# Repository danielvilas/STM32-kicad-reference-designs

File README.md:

# STM32-kicad-reference-designs

{:toc}

Reference Designs for STM32 in KiCad

These projects are designed as reference Design for copy subsheets and reuse wherever needed.

Ideally the board will allways the same (DevelBoard) modified to use the current chip. But as needed the reference design will be updated to use different elements, such as Ethernet, Can Bus, usb.

## Folder structure

The Folders under this repository are defined to follow this standard:
```
 .
├── [FAMILY]
│   ├── [LINE]
|   |   ├──Firmware
|   |   |  └──[*] Platformio Code
|   |   ├──[CHIP]_[Board]
|   |   |  └──[*] Kicad Project
|   |   └──README.MD
│   ├── [LINE] Other line 
|   |   └── ...
|   ...  
│   └──PlatformIo
│       ├──install.sh
│       ├──[Board].json
|       ├──[variantn].h
|       ├──[variantn].cpp
|       └── ... More boards and variants
└──[FAMILY] Other family
├──... More families
...

```
The folder estructure is based on the STM32 organization of theirs chips, this are based on families and lines. This relates to the name of the chip having the code `STM32FFLLCCCC'  where F is the FamiliyCode, L the line and C the chip code.

|Terms|Descritpion|examples|
|:--|:--|:--|
|Family |Stm32 Family | STM32F4, STM32G0 |
|Line| Stm32 Line name, chooses a model within the family| STM32F103, STM32G051|
|Chip| Current Chip, defines package, ram, rom,... inside the line| STM32F103CBT8, STM32G051C8U6|
|Firmware| Platform.io project for all boards on this family. Create envorinments for each| see notes|
|`[CHIP]_[BOARD]`| Kicad Project of board | see notes|
|README.md| each line should have it's own document to explay all the boards, what the firmware does, and the compatible chips (testeds)|
|PlatformIo|On this folder must be all the files to install the boards in PlatformIo.|b|

### Chip compatibility
By default, and as far it is indicated by ST, all the chips with the same package are interchangeables, at least at pcb level. That means that the power pins are on the same posititions and the same for the io ones.

> **_NOTE:_**  Some lines/families needs some minor changes on power pins, but the io pins mantains the positions. Check datasheets

Tested chips, should be on the README.md file of the line.

> **_NOTE:_**  This applies to hardware, not at software. update the firmware accordiling

### Firmware Notes
The firmware should be unique for the line and configured by environments on Platformio. In the case two firmwares are needed, then it will be explained on the README.MD.

The enviroments should be based on the "Generic" boards of platform.io with the defines for use the clock correctly. Even if it is based on another boards, (such as blackpill) in this cases it is correct to have two environments for that board (generic and the original board).

The environments must be explained on the README.md of the line.

The bare minimum firmware must have a blinking led and serial output (UART or USB). If the board has more components (CAN, ETH0,...) the firmware should select them by defines and have the component it's own set of files. 

### Board folder Notes
As stated before, there are compatible chips, cappable of drop-ons replacement. When a fully compatible chip is found, there is no need to copy all the board. But the folder for both chips must exists. When this case ocurrs, ensure that:

* On the original board, include notes on the schematic to include the new chip.
* On the line README.md of the original board, include the chip on the compatible chips found
* On the folder of the new chip, include:
  * Link to the current folder
  * README.MD explaing when was detected, to which, and which versions of the board are tested.
* On the line README.md of the new board document the board is the same of...

> **_NOTE:_**  Remebember that only applies to hardware, the new line must have it's own firmware, with the new chip environment.

## Kicad Project Rules
The objective is to have a series of schemeatic pages to easily import onto new projects.

The main project must only contain:
* Mount holes, or similar
* Debug Leds
* Board related connectors
* Zone for (general) power distribution, or subpage if needed
* Each functional component in one SubPage
* Mapping to the project especific pin/net names

Inside each sub page, one per functional component:
* The bare minimun componentes
* All the required connectors related to the function (SWD, ETH, USB, ...)
* Blocks separated by zones
* Herarchichal pins must be named as low level (chip) possible
* Specific power distribution as a zone, but subpage if needed

Good rules indicate to have all the conectors on the main page, but on this project we search to have a library of schematics ready to use, so it is better to have the required connectors on the same page of the functionality.

## Status of Boards

|Family|Line|Board|Status|
|:--|:--|:--|:--|
|F0|STM32F030|STM32F030K6T6|tested, updated needed|
|F1|STM32F103|STM32F103C8T8|Not implemented, tested old version|
|G0|STM32G051|STM32G051C8U6|Only in design phase|

## Change Log

* 25/05/2021 Initial Commits
  * Copy STM32F103 Devel Board from Digital Trains
* 04/08/2021 Re-Structuration
  * Creation of the structure of folders
  * Update Kicad to sub-pages
  * Added STM32G051
* 03/09/2021 Added F030
  * Added an F030
  * Created Files for board integration on pio

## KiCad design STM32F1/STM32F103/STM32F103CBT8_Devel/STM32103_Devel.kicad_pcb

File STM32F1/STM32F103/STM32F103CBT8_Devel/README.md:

# STM32F103 Devel Board
STM32F103 Board for development with STM32F103CB chip. The intention of this project is to have my own basic board for this chip in order to design custom boards which use the STM32103CB chip.

## Board specs:
* CHIP STM32F103CBT6
  * 128KB Flash / 20 KB RAM
  * 72 MHz Core
  * [https://www.st.com/en/microcontrollers-microprocessors/stm32f103cb.html](https://www.st.com/en/microcontrollers-microprocessors/stm32f103cb.html)
* Board Cristals:
  * HSE Clock: 8 Mhz
  * LSE Clokc: 32.768KHz
* Ports:
  * USB Port
  * SWD 20 pins 2.54
  * SWD 10 pins 1.27
  * PortA and PortB 16 pins 2.54
* 3.3V Regulator:
  * AMS1117-3.3
* Indicator LEDs:
  * 5V
  * 3.3V
  * PB5 (ligh on low)
* Boot selector
  * Boot0 and Boot1 to jumper pins

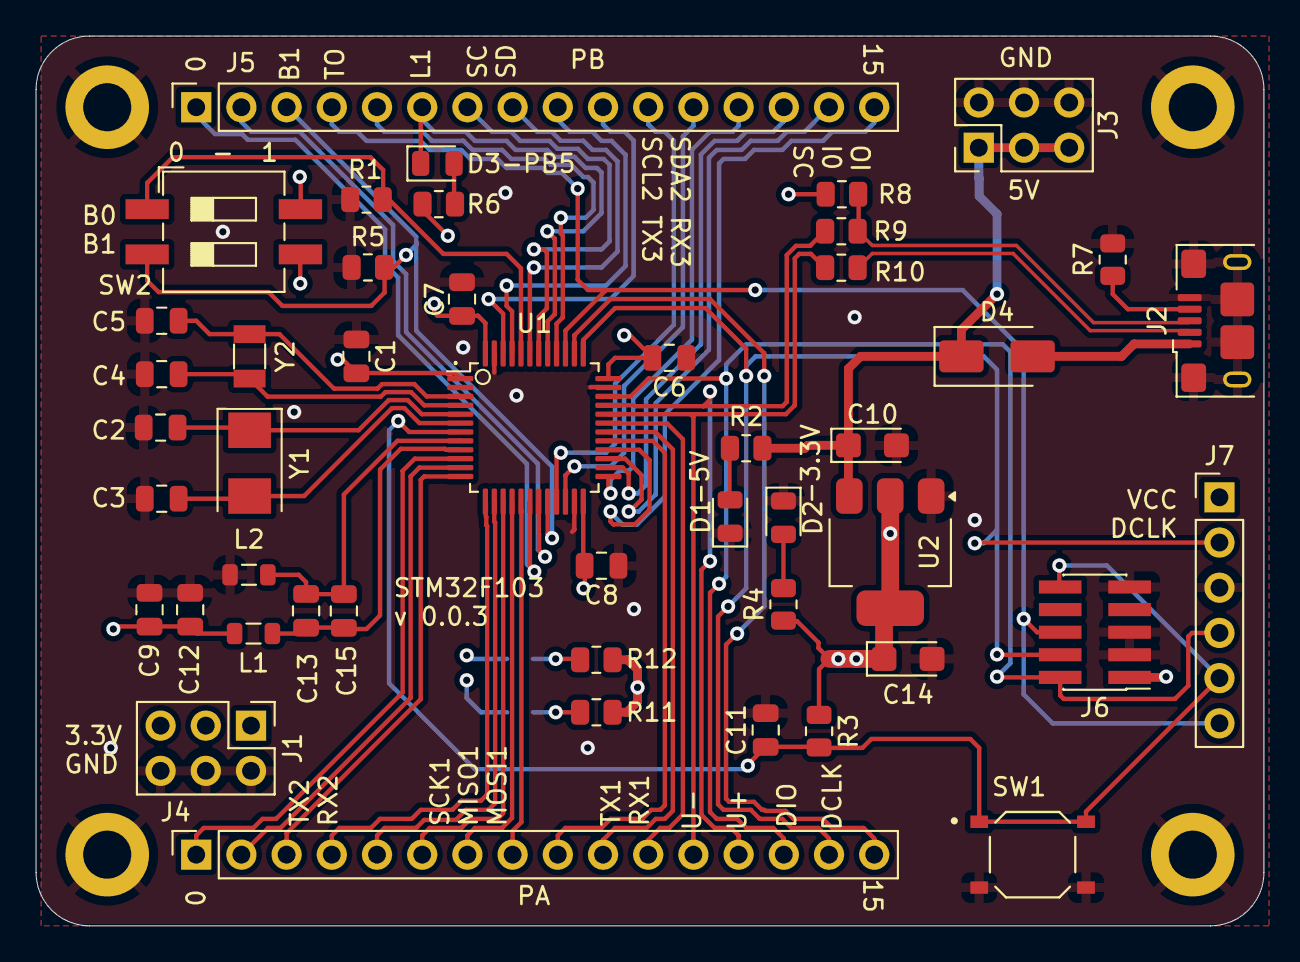
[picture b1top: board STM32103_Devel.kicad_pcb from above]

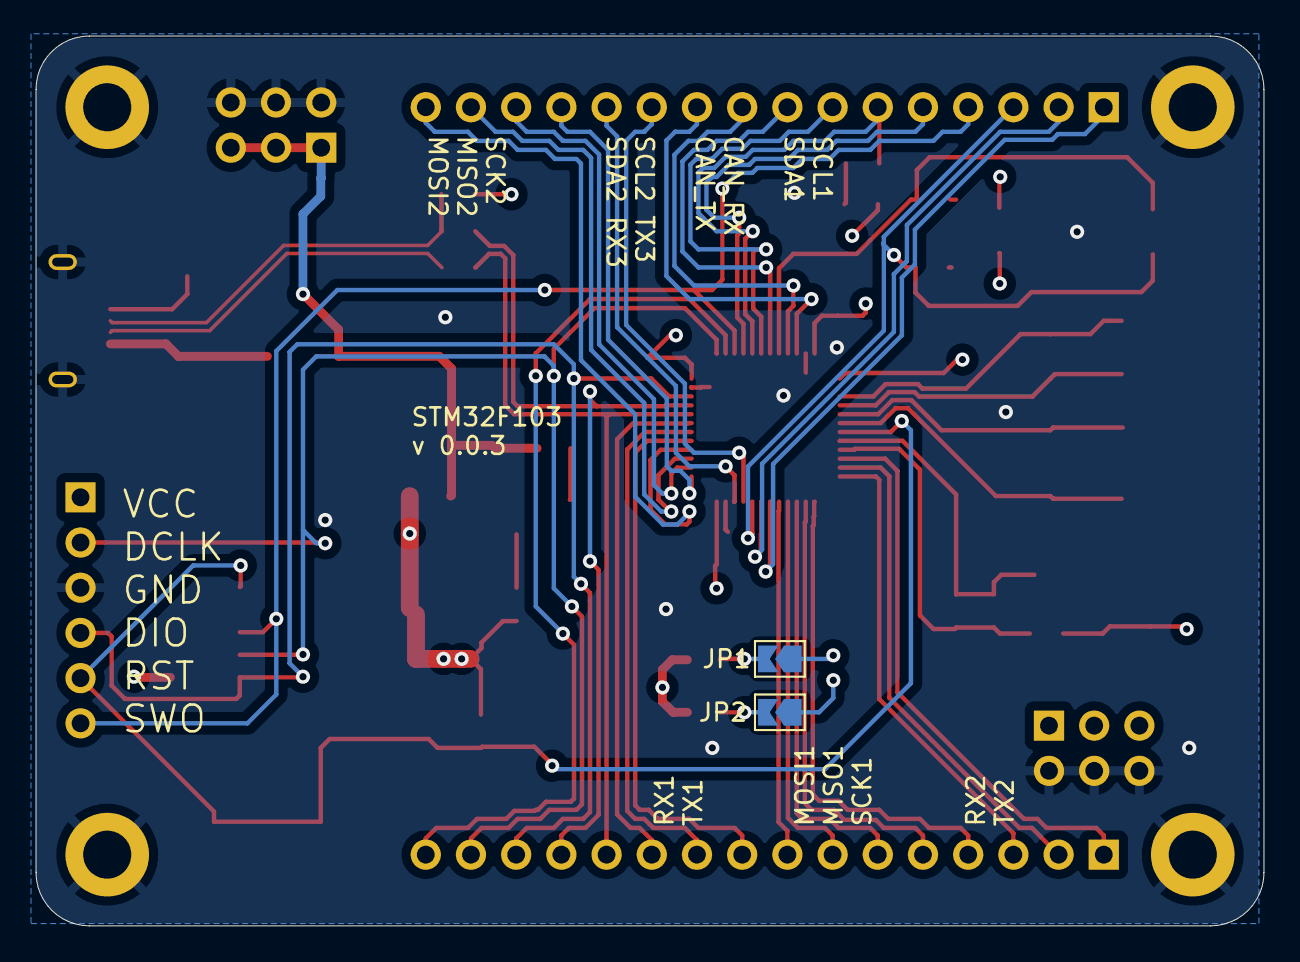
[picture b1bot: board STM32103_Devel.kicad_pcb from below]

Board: 4 copper layers, 69.0 x 50.0 mm, 52 parts (2 on the bottom side), 52 nets.

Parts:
C1, C6, C7, C8, C11: 100nf; C_0805_2012Metric
C2, C3: 20pf; C_0805_2012Metric
C4, C5: 10pf; C_0805_2012Metric
C9, C13: 1uF; C_0805_2012Metric
C10, C14: 10uf; CP_EIA-3216-18_Kemet-A
C12, C15: 10nF; C_0805_2012Metric
D1: RED; LED_0805_2012Metric
D2: BLUE; LED_0805_2012Metric
D3: GREEN; LED_0805_2012Metric
D4: ss14; D_SMA
H1, H2, H3, H4: MountingHole; MountingHole_2.7mm_M2.5_DIN965_Pad
J1, J3: Conn_02x03_Counter_Clockwise; PinHeader_2x03_P2.54mm_Vertical
J2: USB_B_Micro; USB_Micro-B_Amphenol_10118193-0001LF_Horizontal
J4, J5: Conn_01x16; PinSocket_1x16_P2.54mm_Vertical
J6: Conn_02x05 Odd_Even; PinHeader_2x05_P1.27mm_Vertical_SMD
J7: Conn_01x06; PinHeader_1x06_P2.54mm_Vertical
JP1, JP2: sj_o; SolderJumper-2_P1.3mm_Open_TrianglePad1.0x1.5mm
L1, L2: 10uH; L_0805_2012Metric
R1, R2, R3, R5, R11, R12: 10K; R_0805_2012Metric
R4, R6: 1K; R_0805_2012Metric
R7: 100K; R_0805_2012Metric
R8: 1K5; R_0805_2012Metric
R9, R10: 20; R_0805_2012Metric
SW1: SW_Push; SW_PTS526_SM08_SMTR2_LFS
SW2: SW_DIP_x02; SW_DIP_SPSTx02_Slide_6.7x6.64mm_W8.61mm_P2.54mm_LowProfile
U1: STM32F103CBTx; LQFP-48_7x7mm_P0.5mm
U2: AMS1117-3.3; SOT-223-3_TabPin2
Y1: 8MHz; Crystal_SMD_5032-2Pin_5.0x3.2mm
Y2: 32.768kHz; Crystal_SMD_3215-2Pin_3.2x1.5mm

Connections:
+5V: C10.1, D4.1 (K), J3.1, J3.3, J3.5, R2.1, U2.3 (VI)
/PA0: J4.1, U1.10 (PA0)
/PA1: J4.2, U1.11 (PA1)
/PA2: J4.3, U1.12 (PA2)
/PA3: J4.4, U1.13 (PA3)
/PA4: J4.5, U1.14 (PA4)
/PA5: J4.6, U1.15 (PA5)
/PA6: J4.7, U1.16 (PA6)
/PA7: J4.8, U1.17 (PA7)
/PA8: J4.9, U1.29 (PA8)
/PA9: J4.10, U1.30 (PA9)
/PA10: J4.11, U1.31 (PA10)
/PA11: J4.12, R10.2, U1.32 (PA11)
/PA12: J4.13, R9.1, U1.33 (PA12)
/PA13: J4.14, J6.2, J7.4, U1.34 (PA13)
/PA14: J4.15, J6.4, J7.2, U1.37 (PA14)
/PA15: J4.16, U1.38 (PA15)
/PB0: J5.1, U1.18 (PB0)
/PB1: J5.2, U1.19 (PB1)
/PB2: J5.3, R5.1, SW2.2, U1.20 (PB2)
/PB3: J5.4, J6.6, J7.6, U1.39 (PB3)
/PB4: J5.5, U1.40 (PB4)
/PB5: D3.1 (K), J5.6, U1.41 (PB5)
/PB6: J5.7, JP2.1 (A), U1.42 (PB6)
/PB7: J5.8, JP1.1 (A), U1.43 (PB7)
/PB8: J5.9, U1.45 (PB8)
/PB9: J5.10, U1.46 (PB9)
/PB10: J5.11, U1.21 (PB10)
/PB11: J5.12, U1.22 (PB11)
/PB12: J5.13, U1.25 (PB12)
/PB13: J5.14, U1.26 (PB13)
/PB14: J5.15, U1.27 (PB14)
/PB15: J5.16, U1.28 (PB15)
/STM32F103CB/BOOT0: R1.1, SW2.1, U1.44 (BOOT0)
/STM32F103CB/OSC32_IN: C4.1, U1.4 (PC15), Y2.1
/STM32F103CB/OSC32_OUT: C5.1, U1.3 (PC14), Y2.2
/STM32F103CB/OSC_IN: C2.1, U1.5 (PD0), Y1.1
/STM32F103CB/OSC_OUT: C3.1, U1.6 (PD1), Y1.2
/STM32F103CB/RST: C11.1, J6.10, J7.5, R3.2, SW1.1, U1.7 (NRST)
/STM32F103CB/_VDDA: C13.1, C15.1, L1.1, U1.9 (VDDA)
/USB/USB_N: J2.2 (D-), R10.1
/USB/USB_P: J2.3 (D+), R8.1, R9.2
/USB/VCC_USB: D4.2 (A), J2.1 (VBUS)
GND: C1.1, C2.2, C3.2, C4.2, C5.2, C6.1, C7.1, C8.1, C9.2, C10.2, C11.2, C12.2, C14.2, D1.1 (K), D2.1 (K), H1.1, H2.1, H3.1, H4.1, J1.2, J1.4, J1.6, J2.5 (GND), J2.6 (Shield), J3.2, J3.4, J3.6, J6.3, J6.5, J6.9, J7.3, L2.2, R1.2, R5.2, R7.2, SW1.2, U1.23 (VSS), U1.35 (VSS), U1.47 (VSS), U2.1 (GND)
GNDA: C13.2, C15.2, L2.1, U1.8 (VSSA)
unnamed: D1.2 (A), R2.2
unnamed: D2.2 (A), R4.2
unnamed: D3.2 (A), R6.2
unnamed: J2.4 (ID), R7.1
unnamed: JP1.2 (B), R12.2
unnamed: JP2.2 (B), R11.2
VCC: C1.2, C6.2, C7.2, C8.2, C9.1, C12.1, C14.1, J1.1, J1.3, J1.5, J6.1, J7.1, L1.2, R3.1, R4.1, R6.1, R8.2, R11.1, R12.1, SW2.3, SW2.4, U1.1 (VBAT), U1.24 (VDD), U1.36 (VDD), U1.48 (VDD), U2.2 (VO)

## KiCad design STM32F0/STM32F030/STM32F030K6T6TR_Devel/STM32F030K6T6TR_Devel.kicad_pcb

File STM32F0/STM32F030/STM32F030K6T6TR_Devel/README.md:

# STM32F103 Devel Board
STM32F103 Board for development with STM32F103CB chip. The intention of this project is to have my own basic board for this chip in order to design custom boards which use the STM32103CB chip.

## Board specs:
* CHIP STM32F103CBT6
  * 128KB Flash / 20 KB RAM
  * 72 MHz Core
  * [https://www.st.com/en/microcontrollers-microprocessors/stm32f103cb.html](https://www.st.com/en/microcontrollers-microprocessors/stm32f103cb.html)
* Board Cristals:
  * HSE Clock: 8 Mhz
  * LSE Clokc: 32.768KHz
* Ports:
  * USB Port
  * SWD 6 pins 2.54
  * SWD 10 pins 1.27
  * PortA and PortB 16 pins 2.54
* 3.3V Regulator:
  * AMS1117-3.3
* Indicator LEDs:
  * 5V
  * 3.3V
  * PB5 (ligh on low)
* Boot selector
  * Boot0 and Boot1 to jumper pins

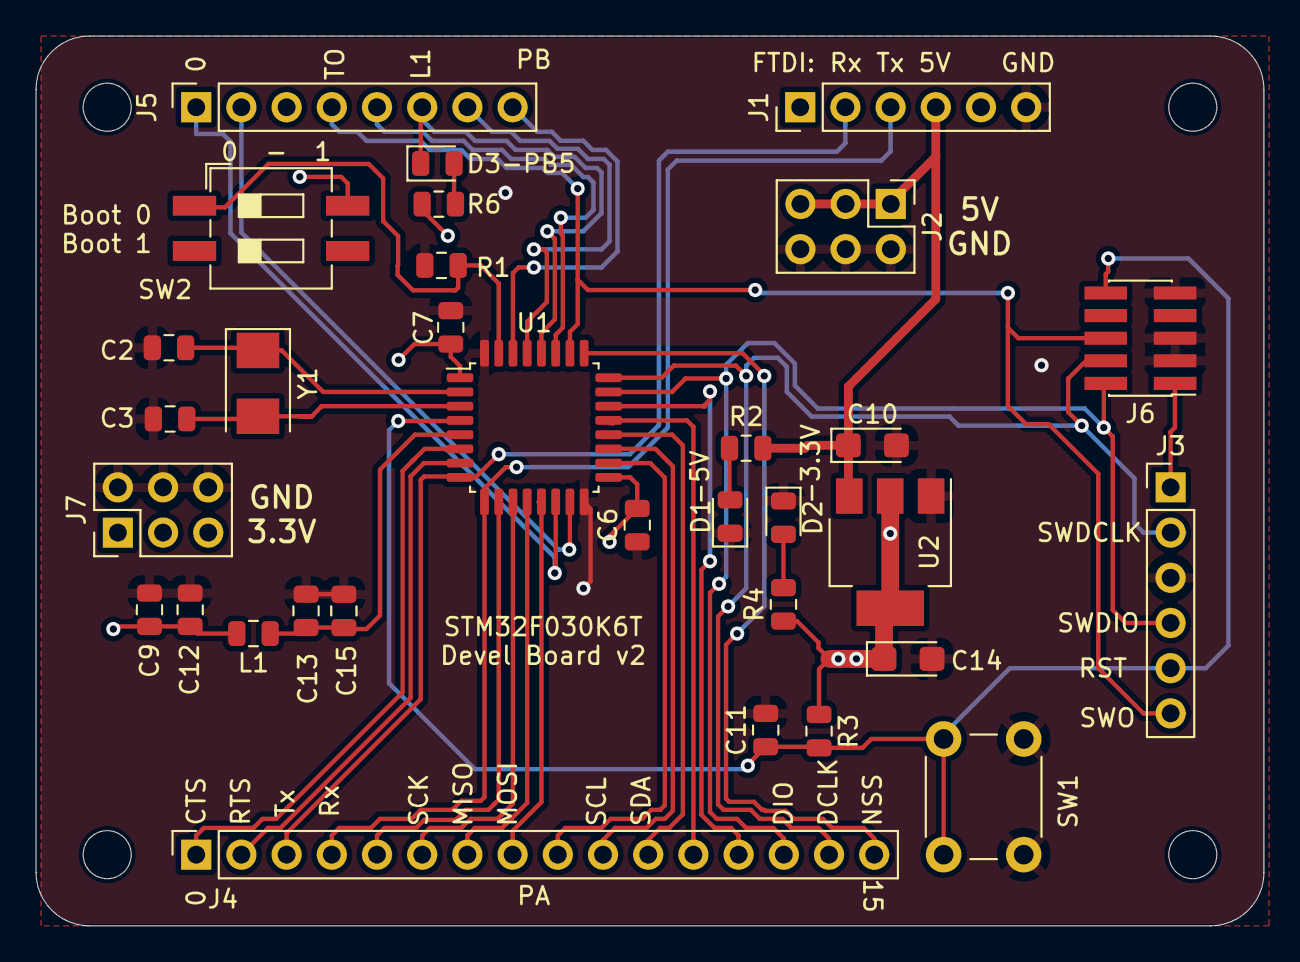
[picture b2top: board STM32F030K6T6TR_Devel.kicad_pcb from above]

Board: 4 copper layers, 69.0 x 50.0 mm, 36 parts (0 on the bottom side), 34 nets.

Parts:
C2, C3: 20pf; C_0805_2012Metric
C6, C7, C11: 100nf; C_0805_2012Metric
C9, C13: 1uF; C_0805_2012Metric
C10, C14: 10uf; CP_EIA-3216-18_Kemet-A
C12, C15: 10nF; C_0805_2012Metric
D1: RED; LED_0805_2012Metric
D2: BLUE; LED_0805_2012Metric
D3: GREEN; LED_0805_2012Metric
H1, H2, H3, H4: MountingHole; MountingHole_2.7mm_M2.5
J1, J3: Conn_01x06; PinHeader_1x06_P2.54mm_Vertical
J2, J7: Conn_02x03_Odd_Even; PinHeader_2x03_P2.54mm_Vertical
J4: Conn_01x16; PinSocket_1x16_P2.54mm_Vertical
J5: Conn_01x08; PinSocket_1x08_P2.54mm_Vertical
J6: Conn_02x05 Odd_Even; PinHeader_2x05_P1.27mm_Vertical_SMD
L1: 10uH; L_0805_2012Metric
R1, R2, R3: 10K; R_0805_2012Metric
R4, R6: 1K; R_0805_2012Metric
SW1: SW_Push; SW_PUSH_6mm
SW2: SW_DIP_x02; SW_DIP_SPSTx02_Slide_6.7x6.64mm_W8.61mm_P2.54mm_LowProfile
U1: STM32F030K6Tx; LQFP-32_7x7mm_P0.8mm
U2: AMS1117-3.3; SOT-223-3_TabPin2
Y1: 8MHz; Crystal_SMD_5032-2Pin_5.0x3.2mm

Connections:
+5V: C10.1, J1.4, J2.1, J2.3, J2.5, R2.1, U2.3 (VI)
/PA0: J4.1, U1.6 (PA0)
/PA1: J4.2, U1.7 (PA1)
/PA2: J1.2, J4.3, U1.8 (PA2)
/PA3: J1.3, J4.4, U1.9 (PA3)
/PA4: J4.5, U1.10 (PA4)
/PA5: J4.6, U1.11 (PA5)
/PA6: J4.7, U1.12 (PA6)
/PA7: J4.8, U1.13 (PA7)
/PA8: J4.9, U1.18 (PA8)
/PA9: J4.10, U1.19 (PA9)
/PA10: J4.11, U1.20 (PA10)
/PA11: J4.12, U1.21 (PA11)
/PA12: J4.13, U1.22 (PA12)
/PA13: J3.4, J4.14, J6.2, U1.23 (PA13)
/PA14: J3.2, J4.15, J6.4, U1.24 (PA14)
/PA15: J4.16, U1.25 (PA15)
/PB0: J5.1, U1.14 (PB0)
/PB1: J5.2, U1.15 (PB1)
/PB3: J3.6, J5.4, J6.6, U1.26 (PB3)
/PB4: J5.5, U1.27 (PB4)
/PB5: D3.1 (K), J5.6, U1.28 (PB5)
/PB6: J5.7, U1.29 (PB6)
/PB7: J5.8, U1.30 (PB7)
/STM32F030K6/BOOT0: R1.1, SW2.1, U1.31 (BOOT0)
/STM32F030K6/OSC_IN: C2.1, U1.2 (PF0), Y1.1
/STM32F030K6/OSC_OUT: C3.1, U1.3 (PF1), Y1.2
/STM32F030K6/RST: C11.1, J3.5, J6.10, R3.2, SW1.1, U1.4 (NRST)
/STM32F030K6/_VDDA: C13.1, C15.1, L1.1, U1.5 (VDDA)
GND: C2.2, C3.2, C6.1, C7.1, C9.2, C10.2, C11.2, C12.2, C13.2, C14.2, C15.2, D1.1 (K), D2.1 (K), J1.6, J2.2, J2.4, J2.6, J3.3, J6.3, J6.5, J6.9, J7.2, J7.4, J7.6, R1.2, SW1.2, U1.16 (VSS), U1.32 (VSS), U2.1 (GND)
unnamed: D1.2 (A), R2.2
unnamed: D2.2 (A), R4.2
unnamed: D3.2 (A), R6.2
VCC: C6.2, C7.2, C9.1, C12.1, C14.1, J3.1, J6.1, J7.1, J7.3, J7.5, L1.2, R3.1, R4.1, R6.1, SW2.4, U1.1 (VDD), U1.17 (VDD), U2.2 (VO)

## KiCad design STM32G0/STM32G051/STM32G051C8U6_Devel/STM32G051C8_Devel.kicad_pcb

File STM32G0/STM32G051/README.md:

# STM32G051
This line does no support USB. So the board is without usb but with a FTDI Header

## Status
This board and firmware is under development. Is a Work In Progress. Not builded.

## Compatibility
This chip is only compatbile with STMG0 line

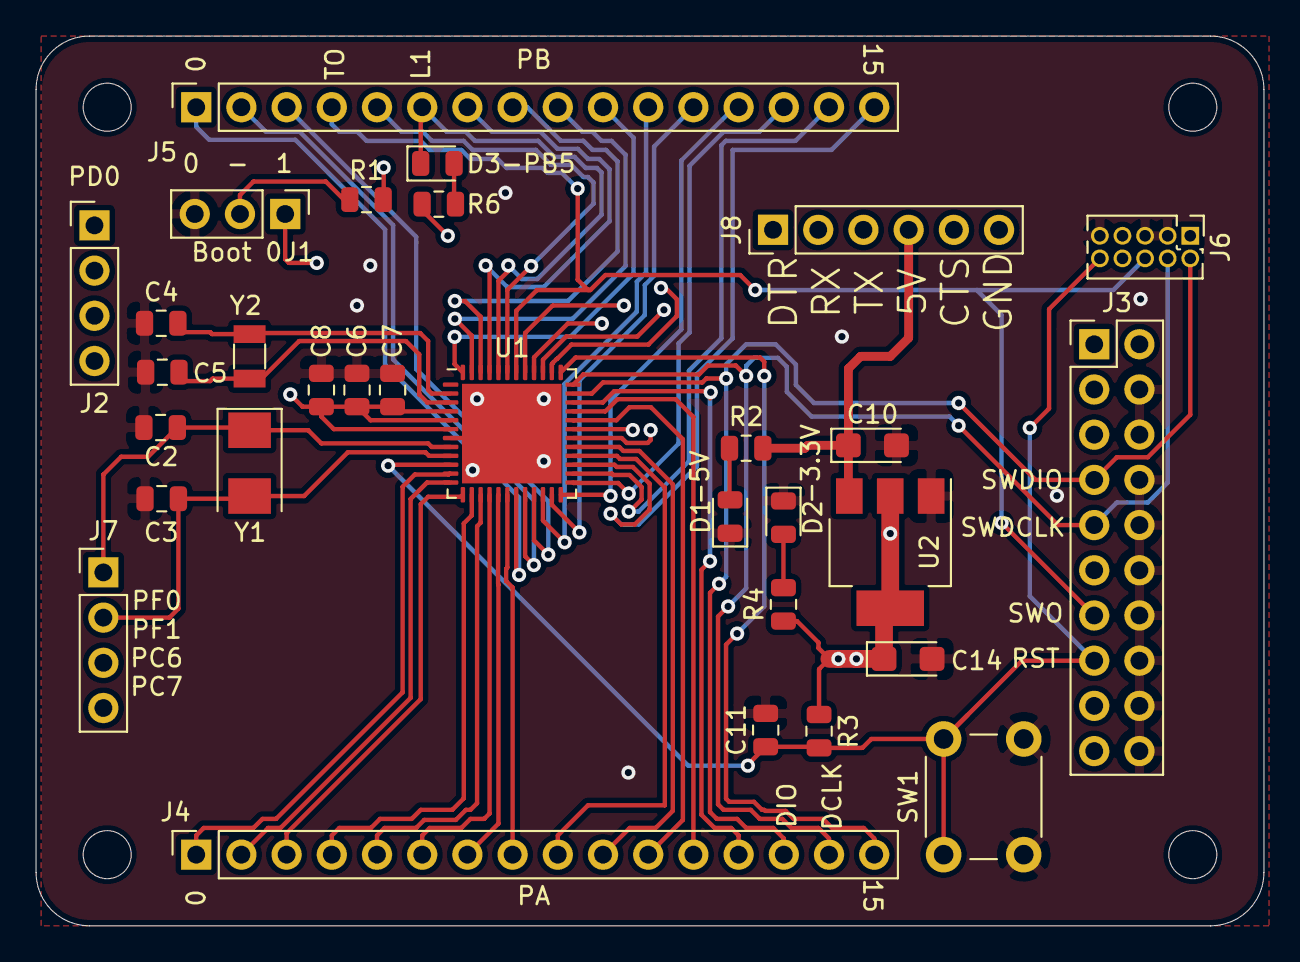
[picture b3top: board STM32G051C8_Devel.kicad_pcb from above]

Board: 4 copper layers, 69.0 x 50.0 mm, 35 parts (0 on the bottom side), 50 nets.

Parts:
C2, C3: 20pf; C_0805_2012Metric
C4, C5: 10pf; C_0805_2012Metric
C6, C7, C8, C11: 100nf; C_0805_2012Metric
C10, C14: 10uf; CP_EIA-3216-18_Kemet-A
D1: RED; LED_0805_2012Metric
D2: BLUE; LED_0805_2012Metric
D3: GREEN; LED_0805_2012Metric
H1, H2, H3, H4: MountingHole; MountingHole_2.7mm_M2.5
J1: Conn_01x03; PinHeader_1x03_P2.54mm_Vertical
J2, J7: Conn_01x04; PinHeader_1x04_P2.54mm_Vertical
J3: Conn_02x10_Odd_Even; PinHeader_2x10_P2.54mm_Vertical
J4, J5: Conn_01x16; PinSocket_1x16_P2.54mm_Vertical
J6: Conn_02x05 Odd_Even; PinHeader_2x05_P1.27mm_Vertical
J8: Conn_01x06; PinHeader_1x06_P2.54mm_Vertical
R1, R2, R3: 10K; R_0805_2012Metric
R4, R6: 1K; R_0805_2012Metric
SW1: SW_Push; SW_PUSH_6mm
U1: STM32G051C8Ux; QFN-48-1EP_7x7mm_P0.5mm_EP5.6x5.6mm
U2: AMS1117-3.3; SOT-223-3_TabPin2
Y1: 8MHz; Crystal_SMD_5032-2Pin_5.0x3.2mm
Y2: Crystal; Crystal_SMD_3215-2Pin_3.2x1.5mm

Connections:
+5V: C10.1, J8.4, R2.1, U2.3
/PA0: J4.1, U1.11
/PA1: J4.2, U1.12
/PA2: J4.3, U1.13
/PA3: J4.4, U1.14
/PA4: J4.5, U1.15
/PA5: J4.6, U1.16
/PA6: J4.7, U1.17
/PA7: J4.8, U1.18
/PA8: J4.9, U1.28
/PA9: J4.10, J8.2, U1.29
/PA10: J4.11, J8.3, U1.32
/PA11: J4.12, U1.33
/PA12: J4.13, U1.34
/PA13: J3.7, J4.14, J6.2, U1.35
/PA14: J3.9, J4.15, J6.4, R1.2, U1.36
/PA15: J4.16, U1.37
/PB0: J5.1, U1.19
/PB1: J5.2, U1.20
/PB2: J5.3, U1.21
/PB3: J3.13, J5.4, J6.6, U1.42
/PB4: J5.5, U1.43
/PB5: D3.1, J5.6, U1.44
/PB6: J5.7, U1.45
/PB7: J5.8, U1.46
/PB8: J5.9, U1.47
/PB9: J5.10, U1.48
/PB10: J5.11, U1.22
/PB11: J5.12, U1.23
/PB12: J5.13, U1.24
/PB13: J5.14, U1.25
/PB14: J5.15, U1.26
/PB15: J5.16, U1.27
/PC6: J7.3, U1.30
/PC7: J7.4, U1.31
/PD0: J2.1, U1.38
/PD1: J2.2, U1.39
/PD2: J2.3, U1.40
/PD3: J2.4, U1.41
/PF0: C2.1, J7.1, U1.8, Y1.1
/PF1: C3.1, J7.2, U1.9, Y1.2
/STM32G051/NRST: C11.1, J3.15, J6.10, R3.2, SW1.1, U1.10
/STM32G051/PC14: C4.1, U1.2, Y2.1
/STM32G051/PC15: C5.1, U1.3, Y2.2
GND: C2.2, C3.2, C4.2, C5.2, C6.1, C7.1, C8.1, C10.2, C11.2, C14.2, D1.1, D2.1, J1.3, J3.4, J3.6, J3.8, J3.10, J3.12, J3.14, J3.16, J3.18, J3.20, J6.3, J6.5, J6.9, SW1.2, U1.7, U1.49, U2.1
unnamed: D1.2, R2.2
unnamed: D2.2, R4.2
unnamed: D3.2, R6.2
unnamed: J1.2, R1.1
VCC: C6.2, C7.2, C8.2, C14.1, J1.1, J3.1, J3.2, J6.1, R3.1, R4.1, R6.1, U1.4, U1.5, U1.6, U2.2

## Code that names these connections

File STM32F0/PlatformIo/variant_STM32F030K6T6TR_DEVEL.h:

/*
 *******************************************************************************
 * Copyright (c) 2020-2021, STMicroelectronics
 * All rights reserved.
 *
 * This software component is licensed by ST under BSD 3-Clause license,
 * the "License"; You may not use this file except in compliance with the
 * License. You may obtain a copy of the License at:
 *                        opensource.org/licenses/BSD-3-Clause
 *
 *******************************************************************************
 */
#pragma once

/*----------------------------------------------------------------------------
 *        STM32 pins number
 *----------------------------------------------------------------------------*/
#define PA0                     PIN_A0
#define PA1                     PIN_A1
#define PA2                     PIN_A2
#define PA3                     PIN_A3
#define PA4                     PIN_A4
#define PA5                     PIN_A5
#define PA6                     PIN_A6
#define PA7                     PIN_A7
#define PA8                     8
#define PA9                     9
#define PA10                    10
#define PA11                    11
#define PA12                    12
#define PA13                    13
#define PA14                    14
#define PA15                    15
#define PB0                     PIN_A8
#define PB1                     PIN_A9
#define PB3                     18
#define PB4                     19
#define PB5                     20
#define PB6                     21
#define PB7                     22
#define PF0                     23
#define PF1                     24

// Alternate pins number
#define PA6_ALT1                (PA6 | ALT1)
#define PA7_ALT1                (PA7 | ALT1)
#define PA7_ALT2                (PA7 | ALT2)
#define PA7_ALT3                (PA7 | ALT3)
#define PB0_ALT1                (PB0 | ALT1)
#define PB1_ALT1                (PB1 | ALT1)
#define PB1_ALT2                (PB1 | ALT2)

#define NUM_DIGITAL_PINS        25
#define NUM_ANALOG_INPUTS       10

// On-board LED pin number
#ifndef LED_BUILTIN
  #define LED_BUILTIN           PB5
#endif

// On-board user button
#ifndef USER_BTN
  #define USER_BTN              PNUM_NOT_DEFINED
#endif

// SPI definitions
#ifndef PIN_SPI_SS
  #define PIN_SPI_SS            PA4
#endif
#ifndef PIN_SPI_SS1
  #define PIN_SPI_SS1           PA15
#endif
#ifndef PIN_SPI_SS2
  #define PIN_SPI_SS2           PNUM_NOT_DEFINED
#endif
#ifndef PIN_SPI_SS3
  #define PIN_SPI_SS3           PNUM_NOT_DEFINED
#endif
#ifndef PIN_SPI_MOSI
  #define PIN_SPI_MOSI          PA7
#endif
#ifndef PIN_SPI_MISO
  #define PIN_SPI_MISO          PA6
#endif
#ifndef PIN_SPI_SCK
  #define PIN_SPI_SCK           PA5
#endif

// I2C definitions
#ifndef PIN_WIRE_SDA
  #define PIN_WIRE_SDA          PA10
#endif
#ifndef PIN_WIRE_SCL
  #define PIN_WIRE_SCL          PA9
#endif

// Timer Definitions
// Use TIM6/TIM7 when possible as servo and tone don't need GPIO output pin
#ifndef TIMER_TONE
  #define TIMER_TONE            TIM14
#endif
#ifndef TIMER_SERVO
  #define TIMER_SERVO           TIM16
#endif

// UART Definitions
#ifndef SERIAL_UART_INSTANCE
  #define SERIAL_UART_INSTANCE  1
#endif

// Default pin used for generic 'Serial' instance
// Mandatory for Firmata
#ifndef PIN_SERIAL_RX
  #define PIN_SERIAL_RX         PA10
#endif
#ifndef PIN_SERIAL_TX
  #define PIN_SERIAL_TX         PA9
#endif

/*----------------------------------------------------------------------------
 *        Arduino objects - C++ only
 *----------------------------------------------------------------------------*/

#ifdef __cplusplus
  // These serial port names are intended to allow libraries and architecture-neutral
  // sketches to automatically default to the correct port name for a particular type
  // of use.  For example, a GPS module would normally connect to SERIAL_PORT_HARDWARE_OPEN,
  // the first hardware serial port whose RX/TX pins are not dedicated to another use.
  //
  // SERIAL_PORT_MONITOR        Port which normally prints to the Arduino Serial Monitor
  //
  // SERIAL_PORT_USBVIRTUAL     Port which is USB virtual serial
  //
  // SERIAL_PORT_LINUXBRIDGE    Port which connects to a Linux system via Bridge library
  //
  // SERIAL_PORT_HARDWARE       Hardware serial port, physical RX & TX pins.
  //
  // SERIAL_PORT_HARDWARE_OPEN  Hardware serial ports which are open for use.  Their RX & TX
  //                            pins are NOT connected to anything by default.
  #ifndef SERIAL_PORT_MONITOR
    #define SERIAL_PORT_MONITOR   Serial
  #endif
  #ifndef SERIAL_PORT_HARDWARE
    #define SERIAL_PORT_HARDWARE  Serial
  #endif
#endif

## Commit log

2021-05-25 STM32F103 Devel Board 0.0.1
2021-05-25 STM32F103 Devel 0.0.2
2021-05-25 Documentation
2021-06-01 Firmware for test
2021-08-03 New Folder Standard
2021-08-03 Kicad Reorg
2021-08-22 Update to dip sw and local VCC
2021-08-22 First version of 030
2021-08-22 Updated Version FootPrint
2021-08-23 Kibot Split on files
2021-09-03 F030K6 Board
2021-09-10 Uart Changes
2021-09-10 Doc updated
2021-09-21 V0 (serial OK)
2024-05-17 STM32F030 Updated to kicad8
2024-06-29 Add mpn for pcbway
2024-06-30 JLCPCB plugin
2024-06-30 StmF103 updated to kicad8 and kibot
2024-06-30 MPN from 030
2024-07-01 Mpn ids
2024-07-01 Mov USB
2024-07-02 Silk Changes
2024-07-04 Power Buttons
2024-07-31 Update Errors
2024-07-31 PCBWAY zip
2024-08-14 I2C pull-Up
2024-08-19 Update MPNS and check
2024-10-12 Docu Actualizada + info silk
2024-10-24 6Pin conector debug
2024-10-28 Revision LCSC
2024-10-28 103 Revision
